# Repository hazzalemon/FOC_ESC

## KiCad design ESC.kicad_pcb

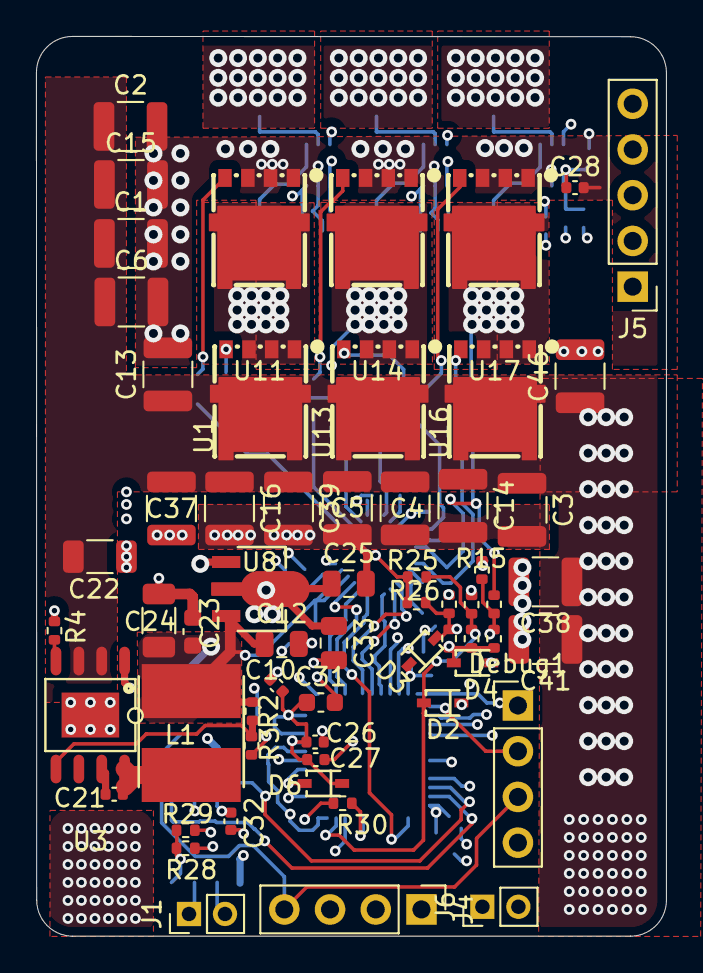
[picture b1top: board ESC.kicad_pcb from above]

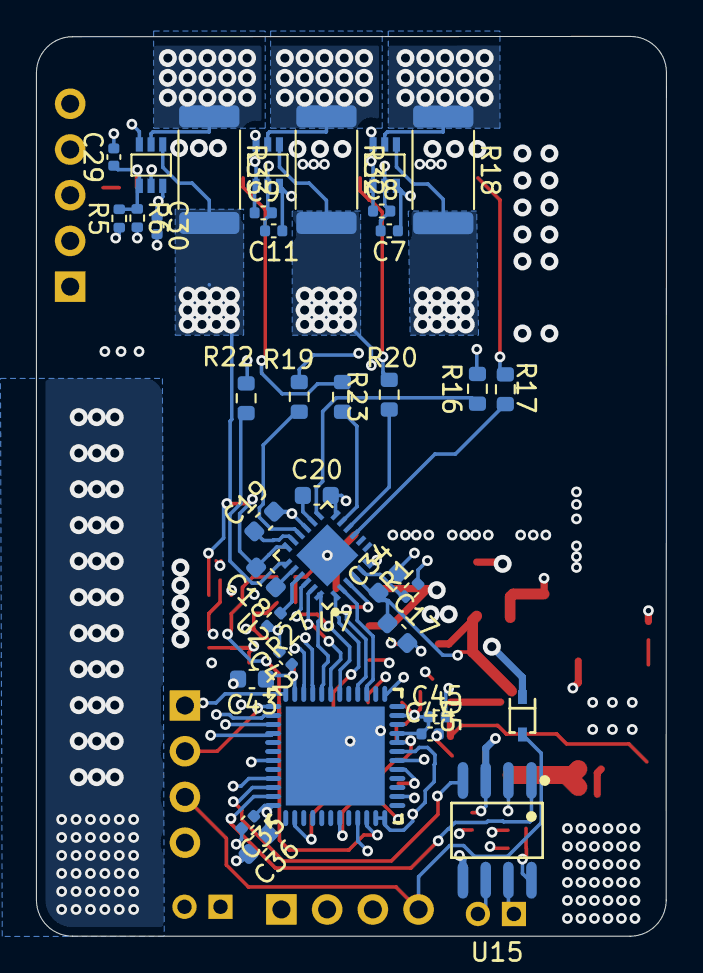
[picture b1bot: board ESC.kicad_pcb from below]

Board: 6 copper layers, 35.0 x 50.0 mm, 98 parts (37 on the bottom side), 61 nets.

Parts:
C1, C2, C3, C4, C5, C6, C13, C14, C15, C16, C37, C38, C39, C41, C46: 4.7u; C_1210_3225Metric
C7, C8, C9, C11, C29, C30: 300n; C_0402_1005Metric
C10, C26, C32, C35, C42: 100n; C_0402_1005Metric
C12, C25, C33: 10u; C_0805_2012Metric
C17, C23, C34: 2.2u; C_0603_1608Metric
C18, C19, C20: 300n; C_0603_1608Metric
C21: 2n; C_0402_1005Metric
C22: 2.2u; C_1206_3216Metric
C24: 47u; C_1206_3216Metric
C27, C28, C45: 1u; C_0402_1005Metric
C31, C36, C43: 4.7u; C_0603_1608Metric
C44: 10n; C_0402_1005Metric
D2, D3, D4, D5, D6: B16WS_C7420327; SOD-323_L1.7-W1.3-LS2.5-FD
Debug1: Conn_01x04; PinHeader_1x04_P2.54mm_Vertical
J1: CAN; PinHeader_1x02_P2.00mm_Vertical
J4: Conn_01x04; PinHeader_1x04_P2.54mm_Vertical
J5: HALL sensors; PinHeader_1x05_P2.54mm_Vertical
J6: UART; PinHeader_1x02_P2.00mm_Vertical
L1: 220u; IND-SMD_L5.8-W5.2
R1, R27: 0; R_0402_1005Metric
R2: 453k; R_0402_1005Metric
R3: 49.9k; R_0402_1005Metric
R4: 100k; R_0402_1005Metric
R5, R6: 63.4k; R_0402_1005Metric
R7, R8, R9, R10, R11, R14: 40k; R_0402_1005Metric
R15, R25, R26: 10k; R_0402_1005Metric
R16, R17, R19, R20, R22, R23: 4; R_0603_1608Metric
R18, R32, R33: 2m; R_2512_6332Metric
R28, R29, R30: DNP; R_0402_1005Metric
U1, U11, U13, U14, U16, U17: SP40N01AGNP; DFN-5_L4.9-W5.9-P1.27-LS6.2-BL
U2: DRV8300DRGER_C3655801; VQFN-24_L4.0-W4.0-P0.50-TL-EP2.5
U3: LM5164DDAR; SO-8_L4.9-W3.9-P1.27-LS6.0-BL-EP
U4, U5, U6: TP181A1-CR; SC70-6_L2.1-W1.3-P0.65-LS2.3-BL
U7: STM32G431CBU6; UFQFPN-48_L7.0-W7.0-P0.50-BL-EP
U8: AMS1117-3.3(XBLW); SOT-89-3_L4.5-W2.5-P1.50-LS4.2-BR
U15: SN65HVD234DR; SOIC-8_L4.9-W3.9-P1.27-LS6.0-BL

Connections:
+3.3V: C7.1, C10.1, C11.1, C25.1, C26.1, C27.1, C30.1, C31.1, C32.1, C33.1, C35.1, C36.1, C42.1, C43.1, C44.1, C45.1, D2.2 (K), D3.2 (K), D4.2 (K), D6.2 (K), J5.4, R5.1, R28.1, R30.1, U4.3 (V+), U5.3 (V+), U6.3 (V+), U7.20 (VREF+), U7.21 (VDDA), U7.23 (VDD), U7.35 (VDD), U7.48 (VDD), U8.2 (VOUT), U15.3 (VCC), U15.5 (EN)
+12V: C12.1, C17.1, C23.2, C24.2, C34.1, D5.2 (K), L1.2, R2.1, U2.4 (GVDD), U8.3 (VIN)
/FETs/Cur_A: U6.6 (OUT), U7.9 (PA1)
/FETs/Cur_B: U5.6 (OUT), U7.14 (PA6)
/FETs/Cur_C: U4.6 (OUT), U7.25 (PB12)
/FETs/ZERO_CROSS_A: D6.1 (A), R7.2, R9.1, R15.2, U7.17 (PB0)
/FETs/ZERO_CROSS_B: D2.1 (A), R8.2, R10.1, R25.2, U7.10 (PA2)
/FETs/ZERO_CROSS_C: D3.1 (A), R11.1, R14.2, R26.2, U7.18 (PB1)
/FETs/amp_vref: C8.1, C9.1, C28.1, C29.1, R5.2, R6.1, U4.1 (REF), U5.1 (REF), U6.1 (REF)
/FETs/phase_A: C18.2, R9.2, R33.2, U2.18 (SHA), U6.4 (IN+), U16.1 (S), U16.2 (S), U16.3 (S), U17.5 (D)
/FETs/phase_A_out: R33.1, U6.5 (IN-)
/FETs/phase_B: C19.2, R10.2, R32.2, U2.15 (SHB), U5.4 (IN+), U13.1 (S), U13.2 (S), U13.3 (S), U14.5 (D)
/FETs/phase_B_out: R32.1, U5.5 (IN-)
/FETs/phase_C: C20.2, R11.2, R18.2, U1.1 (S), U1.2 (S), U1.3 (S), U2.12 (SHC), U4.4 (IN+), U11.5 (D)
/FETs/phase_C_out: R18.1, U4.5 (IN-)
/FETs/pseudo neutral: D4.1 (A), R7.1, R8.1, R14.1, U7.11 (PA3), U7.12 (PA4), U7.19 (PB2)
/GHA: R22.1, U2.19 (GHA)
/GHB: R19.1, U2.16 (GHB)
/GHC: R16.1, U2.13 (GHC)
/GLA: R23.1, U2.11 (GLA)
/GLB: R20.1, U2.10 (GLB)
/GLC: R17.1, U2.9 (GLC)
/gate_driver/sig_AH: U2.22 (INHA), U7.30 (PA8)
/gate_driver/sig_AL: U2.1 (INLA), U7.2 (PC13)
/gate_driver/sig_CH: U2.24 (INHC), U7.32 (PA10)
/gate_driver/sig_CL: U2.3 (INLC), U7.28 (PB15)
/gate_driver/sig__BH: U2.23 (INHB), U7.31 (PA9)
/gate_driver/sig__BL: U2.2 (INLB), U7.27 (PB14)
/microcontroller/5V: D5.1 (A), Debug1.3, J4.4
/microcontroller/CAN_RX: U7.46 (PB8-BOOT0), U15.4 (R)
/microcontroller/CAN_TX: U7.47 (PB9), U15.1 (D)
/microcontroller/DEBUG_SWCLK: Debug1.2, U7.37 (PA14)
/microcontroller/DEBUG_SWDIO: Debug1.1, U7.36 (PA13)
/microcontroller/HALL_1: J5.1, U7.45 (PB7)
/microcontroller/HALL_2: J5.2, U7.38 (PA15)
/microcontroller/HALL_3: J5.3, U7.43 (PB5)
/microcontroller/UART_RX: J6.2, U7.40 (PC11)
/microcontroller/UART_TX: J6.1, U7.39 (PC10)
/microcontroller/USB_D+: J4.2, U7.34 (PA12)
/microcontroller/USB_D-: J4.3, U7.33 (PA11)
GND: C1.2, C2.2, C3.2, C4.2, C5.2, C6.2, C7.2, C8.2, C9.2, C10.2, C11.2, C12.2, C13.2, C14.2, C15.2, C16.2, C17.2, C22.2, C23.1, C24.1, C25.2, C26.2, C27.2, C28.2, C29.2, C30.2, C31.2, C32.2, C33.2, C34.2, C35.2, C36.2, C37.2, C38.2, C39.2, C41.2, C42.2, C43.2, C44.2, C45.2, C46.2, Debug1.4, J4.1, J5.5, R1.2, R3.2, R4.2, R6.2, R15.1, R25.1, R26.1, R27.2, R29.2, U2.6 (GND), U2.25 (EP), U3.1 (GND), U3.9 (EP), U4.2 (GND), U5.2 (GND), U6.2 (GND), U7.49 (EP), U8.1 (GND), U11.1 (S), U11.2 (S), U11.3 (S), U14.1 (S), U14.2 (S), U14.3 (S), U15.2 (GND), U17.1 (S), U17.2 (S), U17.3 (S)
unnamed: J1.1, U15.7 (CANH)
unnamed: J1.2, U15.6 (CANL)
unnamed: R16.2, U1.4 (G)
unnamed: C18.1, U2.20 (BSTA)
unnamed: C19.1, U2.17 (BSTB)
unnamed: C20.1, U2.14 (BSTC)
unnamed: R27.1, U2.21 (DT)
unnamed: R1.1, U2.5 (MODE)
unnamed: C21.1, U3.7 (BST)
unnamed: R2.2, R3.1, U3.5 (FB)
unnamed: R4.1, U3.4 (RON)
unnamed: C21.2, L1.1, U3.8 (SW)
unnamed: R30.2, U7.7 (PG10-NRST)
unnamed: R17.2, U11.4 (G)
unnamed: R19.2, U13.4 (G)
unnamed: R20.2, U14.4 (G)
unnamed: R28.2, R29.1, U15.8 (RS)
unnamed: R22.2, U16.4 (G)
unnamed: R23.2, U17.4 (G)
VDD: C1.1, C2.1, C3.1, C4.1, C5.1, C6.1, C13.1, C14.1, C15.1, C16.1, C22.1, C37.1, C38.1, C39.1, C41.1, C46.1, U1.5 (D), U3.2 (VIN), U3.3 (EN/UVLO), U13.5 (D), U16.5 (D)
